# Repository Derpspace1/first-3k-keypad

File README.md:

# My First Keypad
 A 4 key keypad pcb in the same arrangement as arrow keys

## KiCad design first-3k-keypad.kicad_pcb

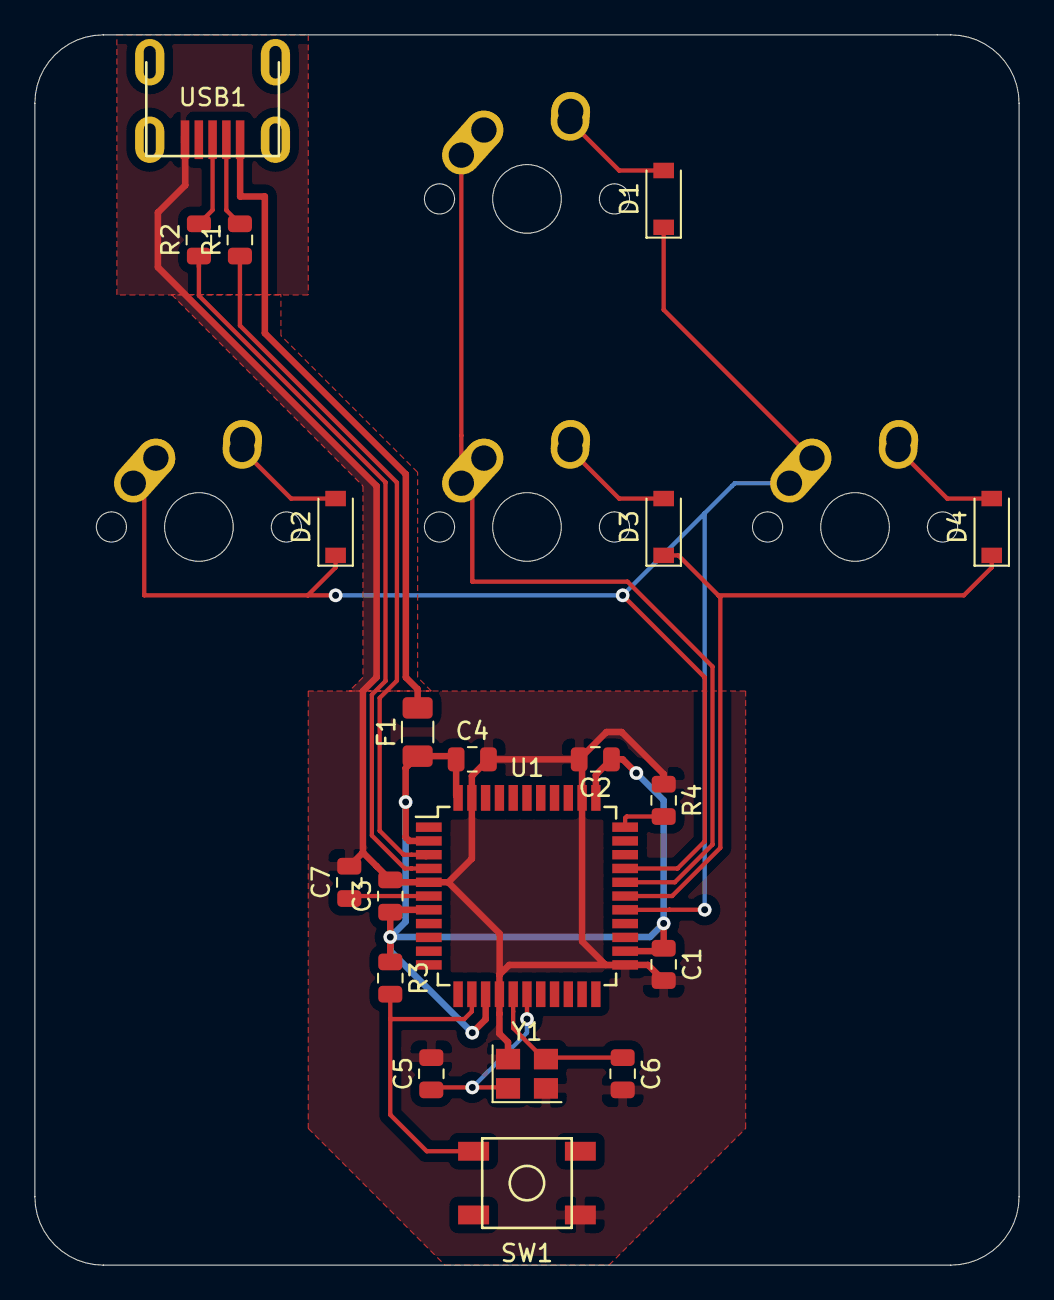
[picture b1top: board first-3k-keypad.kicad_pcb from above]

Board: 2 copper layers, 57.1 x 71.4 mm, 24 parts (0 on the bottom side), 18 nets.

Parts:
C1, C2, C3: 0.1uf; C_0805_2012Metric
C4: 10uf; C_0805_2012Metric
C5, C6: 22pF; C_0805_2012Metric
C7: 1uF; C_0805_2012Metric
D1, D2, D3, D4: D_Small; D_SOD-123
F1: 500mA; Fuse_1206_3216Metric
MX1, MX2, MX3, MX4: MX-NoLED; MX-1U-NoLED
R1, R2: 22; R_0805_2012Metric
R3, R4: 10k; R_0805_2012Metric
SW1: SW_Push; SKQG-1155865
U1: ATmega32U4-AU; TQFP-44_10x10mm_P0.8mm
USB1: Molex-0548190589
Y1: 16MHz; Crystal_SMD_3225-4Pin_3.2x2.5mm

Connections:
+5V: C1.1, C2.1, C3.1, C4.1, F1.1, R3.1, U1.2, U1.7, U1.14, U1.24, U1.34, U1.44
COL0: MX1.1, MX3.1, U1.29
COL1: D1.1, D2.1, D4.2, MX2.1, MX4.1, MX4.2, U1.27, U1.30
D+: R2.2, USB1.3
D-: R1.2, USB1.4
GND: C1.2, C2.2, C3.2, C4.2, C5.2, C6.2, C7.2, R4.1, SW1.1, U1.5, U1.15, U1.23, U1.35, U1.43, USB1.1, Y1.2, Y1.4
unnamed: C5.1, U1.17, Y1.1
unnamed: C6.1, U1.16, Y1.3
unnamed: C7.1, U1.6
unnamed: D1.2, MX1.2
unnamed: D2.2, MX2.2
unnamed: D3.2, MX3.2
unnamed: R1.1, U1.3
unnamed: R2.1, U1.4
unnamed: R3.2, SW1.2, U1.13
unnamed: R4.2, U1.33
ROW1: D3.1, D4.1, U1.28
VCC: F1.2, USB1.5

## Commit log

2022-10-07 Add submodules
2022-10-20 Finished Schematic
2022-10-20 Footprints Assigned
2022-10-20 Finished PCB
2022-10-20 Fixed outline
2022-10-20 Minor Edits
2022-10-20 Actually Finished this time
2022-10-20 4k Keypad
2022-10-21 New Trace Layout
2022-10-21 Gounds, deco
2022-10-21 Gerbers
2022-10-21 Updated Traces
2022-10-22 Gerbers 2
2022-10-24 ujih
2022-10-28 3552662432235523235
2022-10-29 updated Gerbers.zip 2
